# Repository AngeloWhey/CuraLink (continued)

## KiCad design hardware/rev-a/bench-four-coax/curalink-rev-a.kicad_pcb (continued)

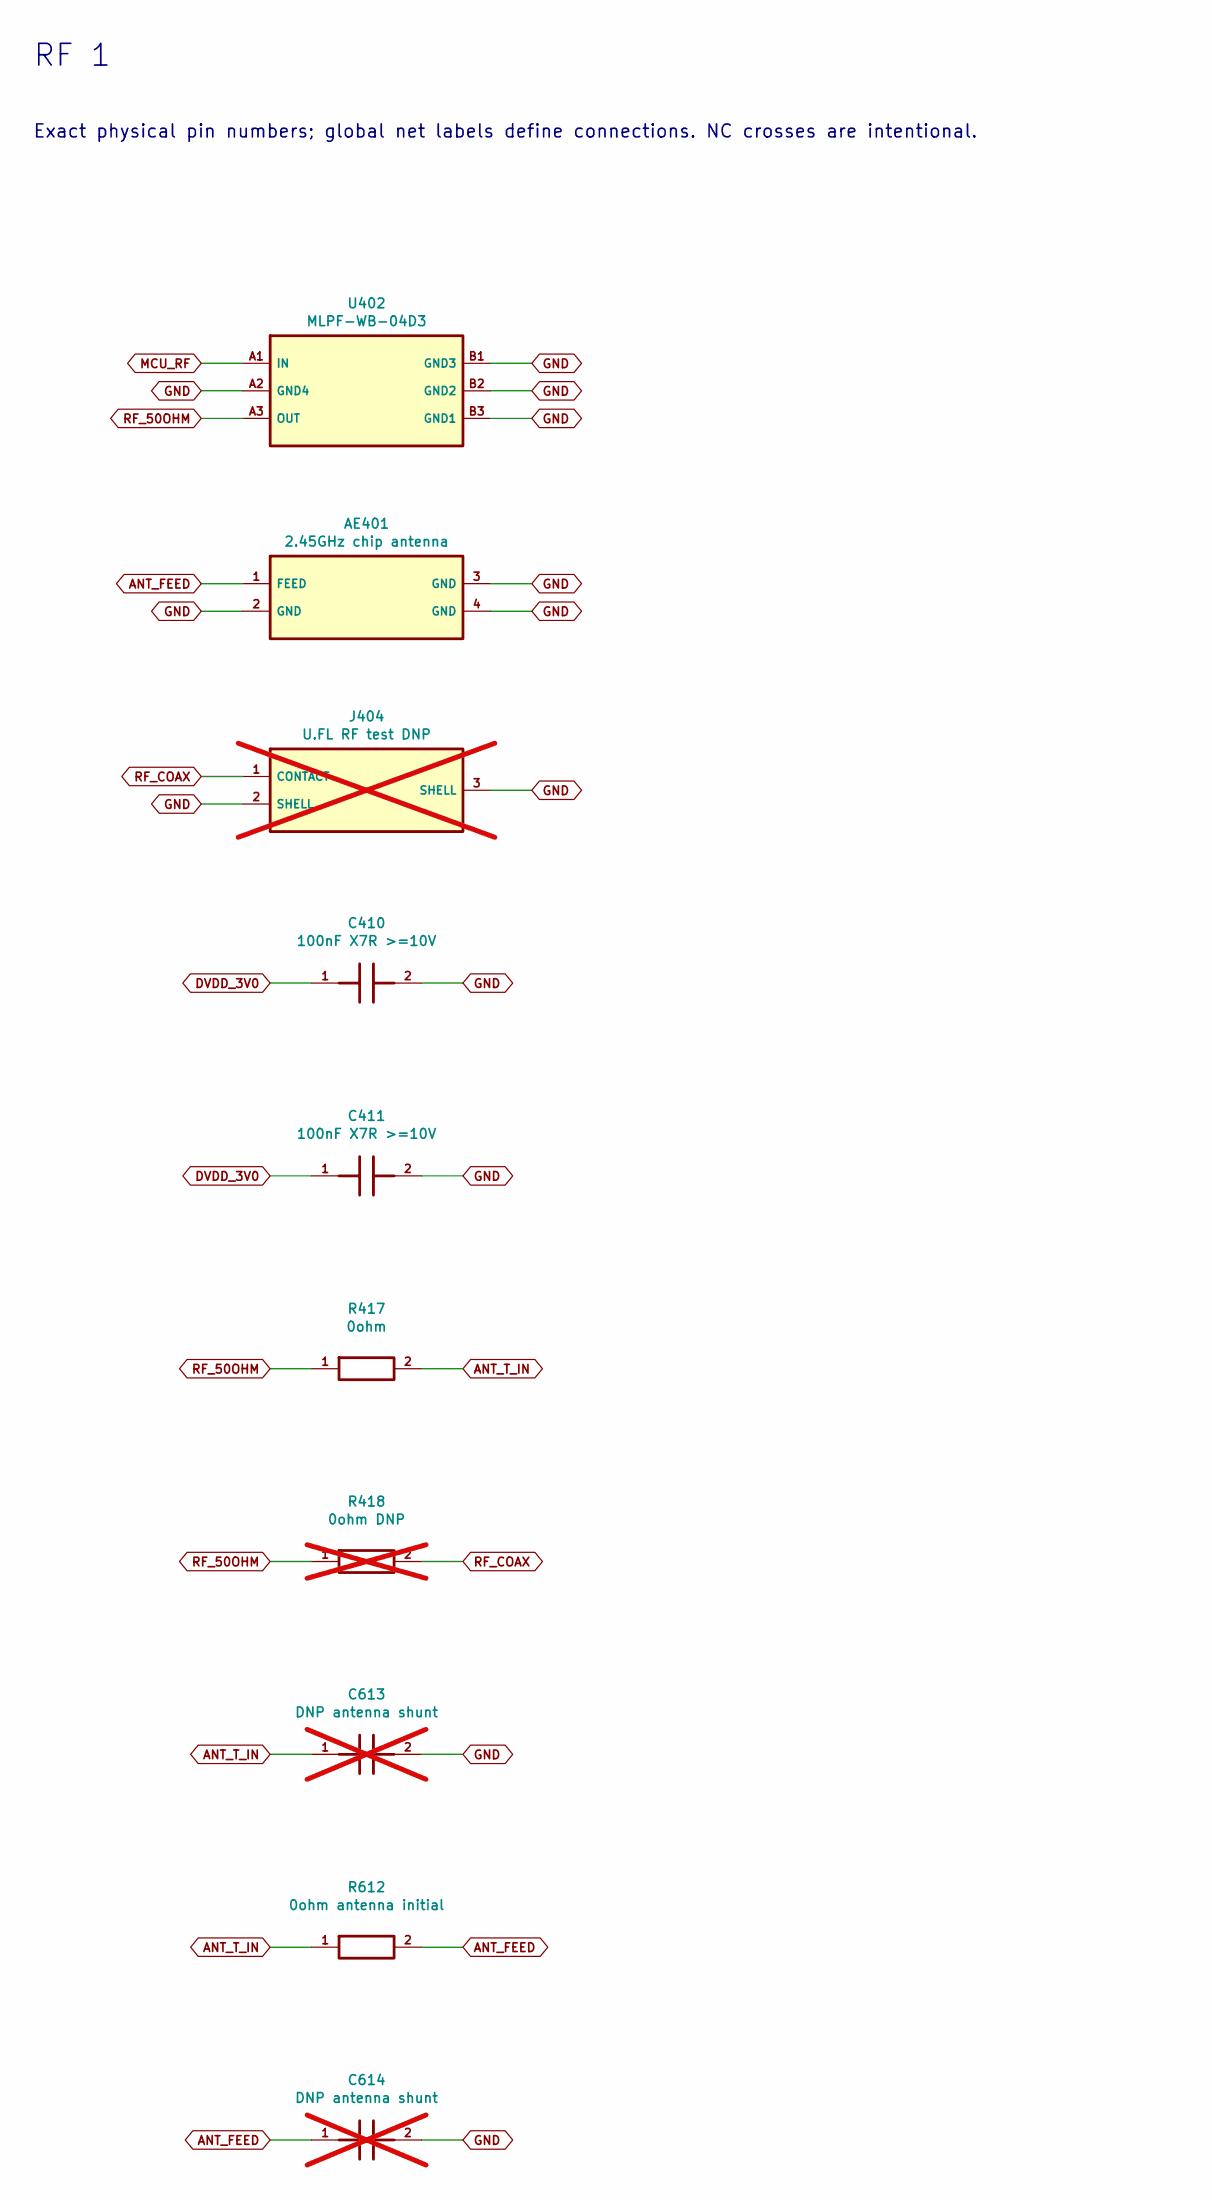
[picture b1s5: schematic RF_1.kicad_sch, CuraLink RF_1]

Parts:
AE401: 2.45GHz chip antenna; Johanson_2450AT18D0100001E; MPN 2450AT18D0100001E; LCSC C7450310
C410, C411: 100nF X7R >=10V; C_0402_1005Metric; MPN GRM155R71C104KA88D; LCSC C71629
C613, C614: DNP antenna shunt; C_0402_1005Metric; not fitted
J404: U.FL RF test DNP; UFL_Hirose_1SIG_2GND_3GND; MPN U.FL-R-SMT-1(80); LCSC C88374; not fitted
R417: 0ohm; R_0402_1005Metric; MPN 0402WGF0000TCE; LCSC C17168
R418: 0ohm DNP; R_0402_1005Metric; MPN 0402WGF0000TCE; LCSC C17168; not fitted
R612: 0ohm antenna initial; R_0402_1005Metric; MPN 0402WGF0000TCE; LCSC C17168
U402: MLPF-WB-04D3; MPN MLPF-WB-04D3; LCSC C22378853

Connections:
ANT_FEED: AE401.1 (FEED), C614.1, R612.2
ANT_T_IN: C613.1, R417.2, R612.1
DVDD_3V0: C410.1, C411.1; also elsewhere on the board
GND: AE401.2 (GND), AE401.3 (GND), AE401.4 (GND), C410.2, C411.2, C613.2, C614.2, J404.2 (SHELL), J404.3 (SHELL), U402.A2 (GND4), U402.B1 (GND3), U402.B2 (GND2), U402.B3 (GND1); also elsewhere on the board
MCU_RF: U402.A1 (IN); also elsewhere on the board
RF_50OHM: R417.1, R418.1, U402.A3 (OUT)
RF_COAX: J404.1 (CONTACT), R418.2

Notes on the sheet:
RF 1
Exact physical pin numbers; global net labels define connections. NC crosses are intentional.

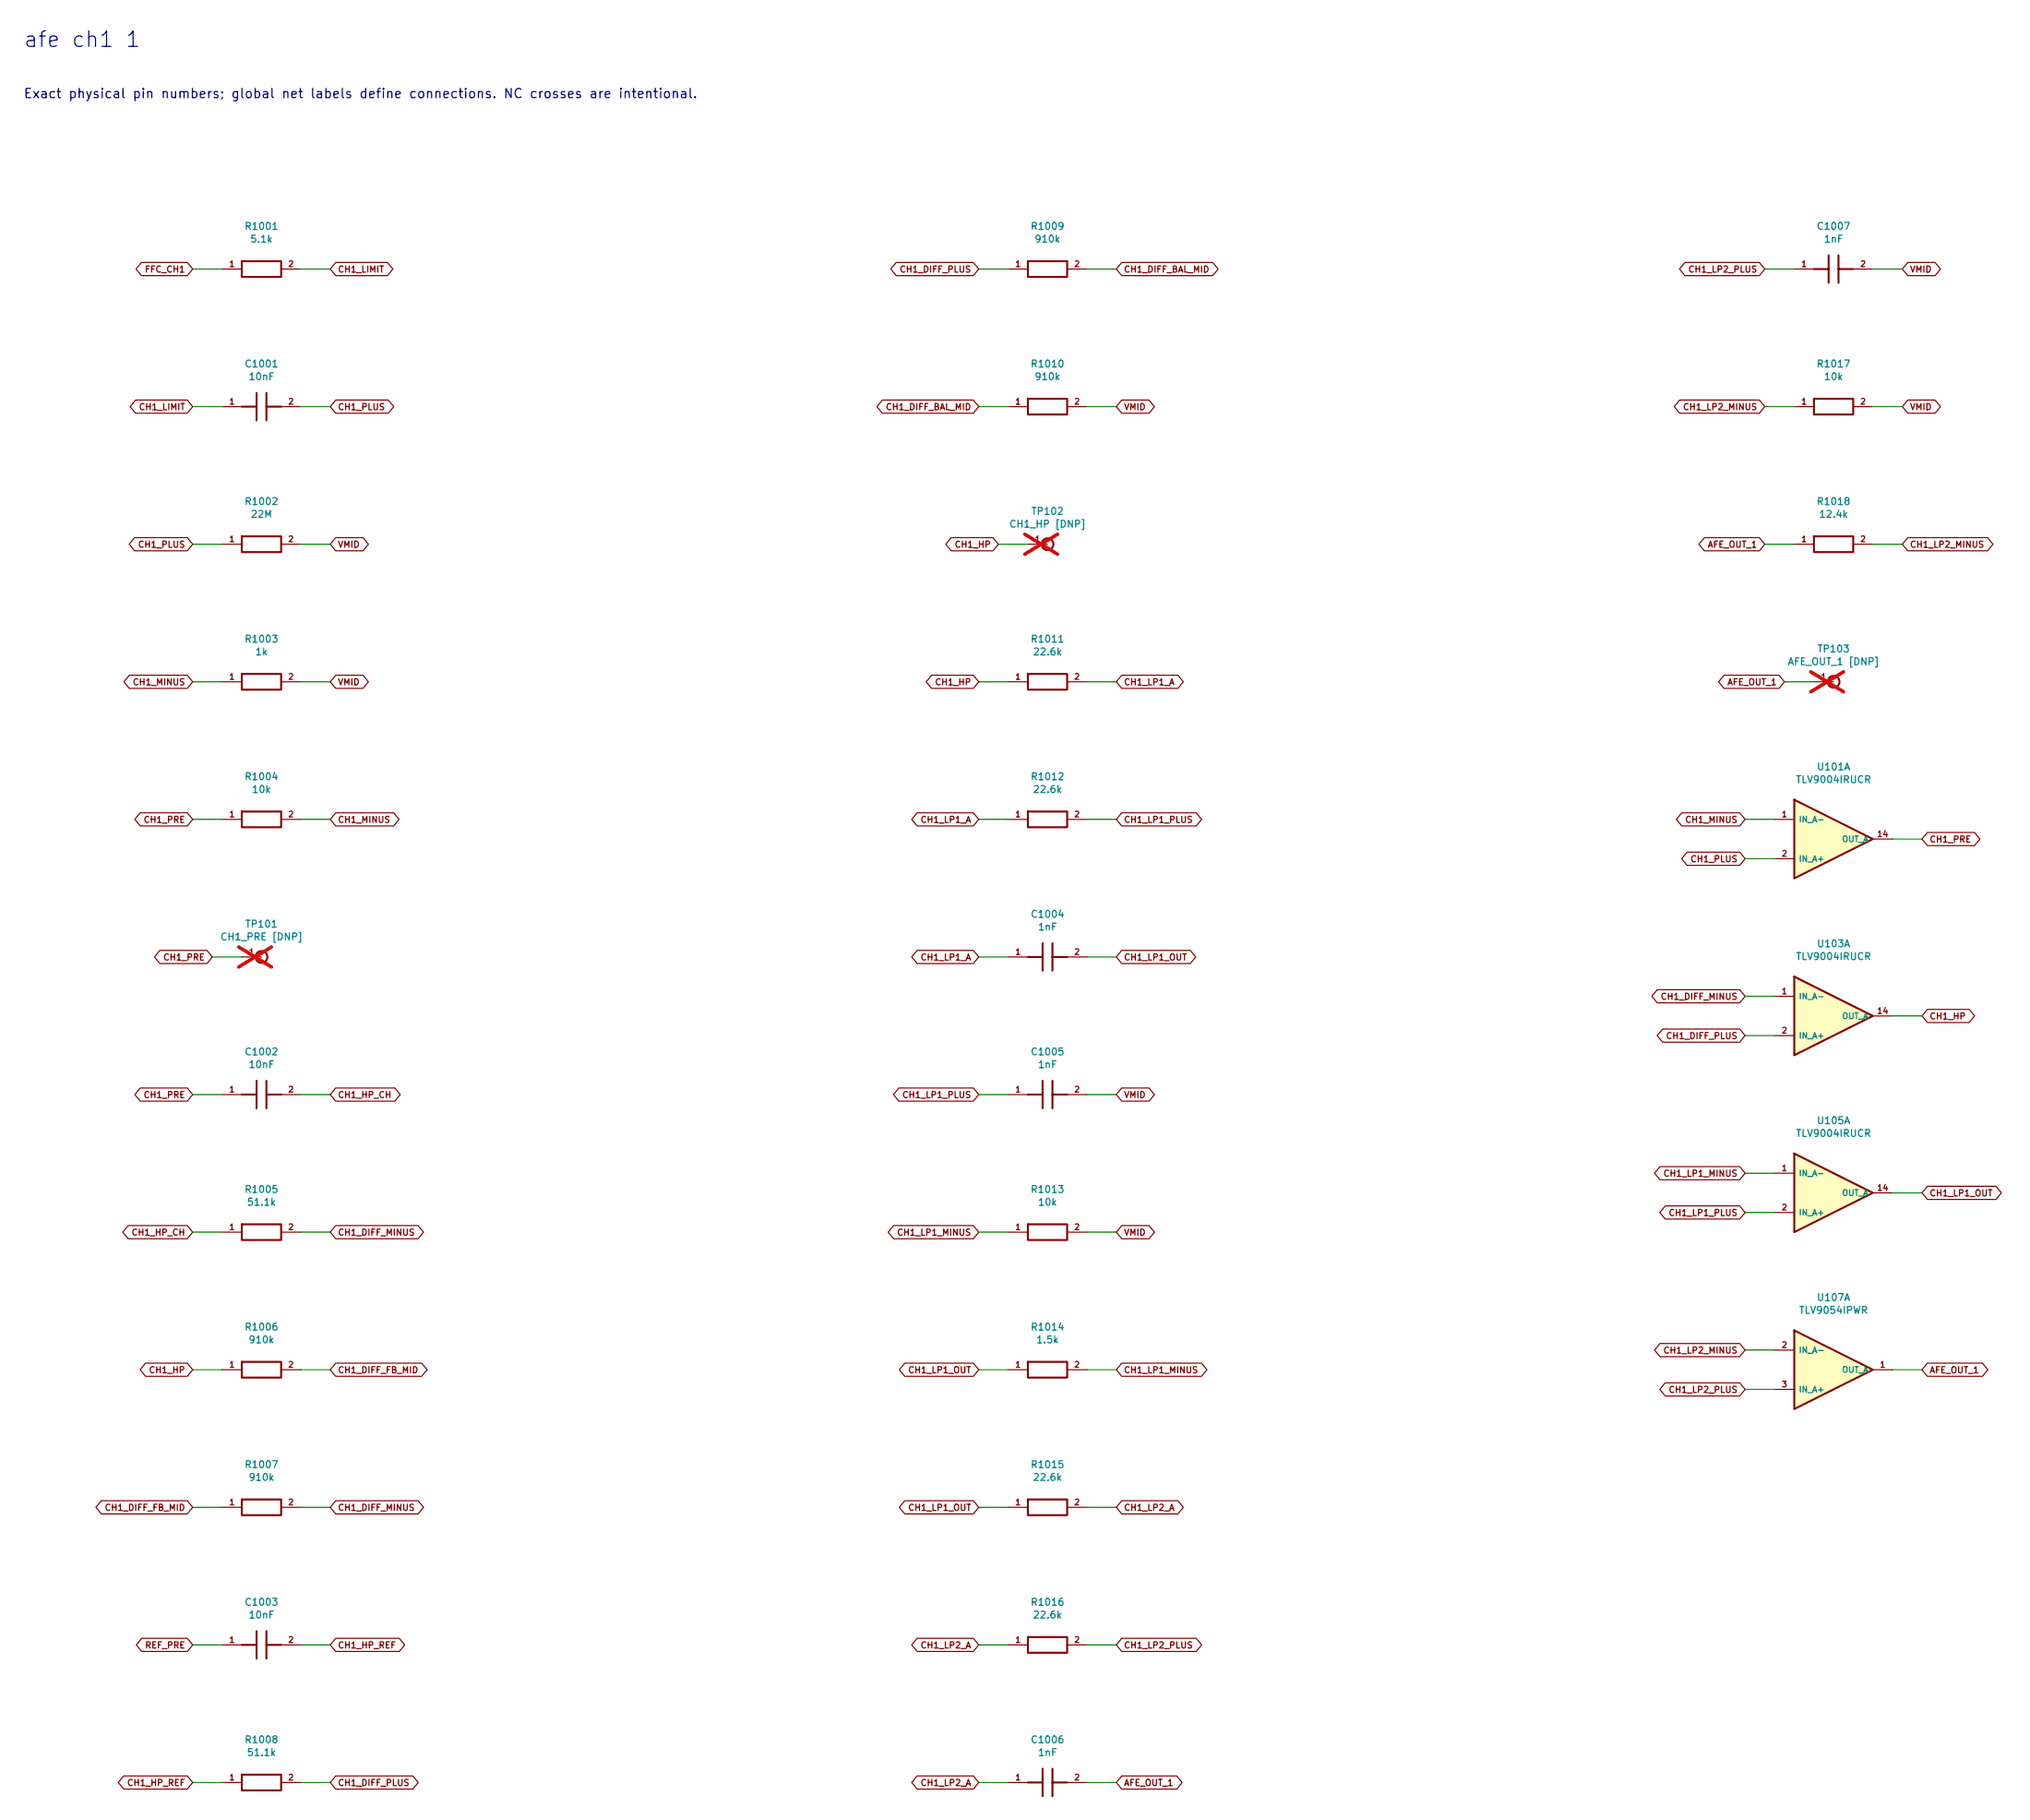
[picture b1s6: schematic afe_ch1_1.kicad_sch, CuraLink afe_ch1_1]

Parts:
C1001, C1002, C1003: 10nF; C_0603_1608Metric; MPN C0603C103F3GACTU; LCSC C2167903
C1004, C1005, C1006, C1007: 1nF; C_0603_1608Metric; MPN 0603CG102F500NT; LCSC C507408
R1001: 5.1k; R_0402_1005Metric; MPN 0402WGF5101TCE; LCSC C25905
R1002: 22M; R_0402_1005Metric; MPN 0402WGF2205TCE; LCSC C407703
R1003: 1k; R_0402_1005Metric; MPN RT0402BRD071KL; LCSC C852624
R1004, R1013, R1017: 10k; R_0402_1005Metric; MPN RT0402BRD0710KL; LCSC C190095
R1005, R1008: 51.1k; R_0402_1005Metric; MPN RT0402BRD0751K1L; LCSC C852827
R1006, R1007, R1009, R1010: 910k; R_0603_1608Metric; MPN ARG03BTC9103; LCSC C2686431
R1011, R1012, R1015, R1016: 22.6k; R_0402_1005Metric; MPN 0402WGF2262TCE; LCSC C26960
R1014: 1.5k; R_0402_1005Metric; MPN RT0402BRD071K5L; LCSC C281775
R1018: 12.4k; R_0402_1005Metric; MPN RT0402BRD0712K4L; LCSC C723611
TP101: CH1_PRE [DNP]; TestPoint_Pad_D1.0mm; not fitted
TP102: CH1_HP [DNP]; TestPoint_Pad_D1.0mm; not fitted
TP103: AFE_OUT_1 [DNP]; TestPoint_Pad_D1.0mm; not fitted
U101, U103, U105: TLV9004IRUCR; TLV_RUC14_X2QFN_2x2mm_NoEP; MPN TLV9004IRUCR; LCSC C2058192
U107: TLV9054IPWR; TSSOP-14_4.4x5mm_P0.65mm; MPN TLV9054IPWR; LCSC C2057744

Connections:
AFE_OUT_1: C1006.2, R1018.1, TP103.1, U107.1 (OUT_A); also elsewhere on the board
CH1_DIFF_BAL_MID: R1009.2, R1010.1
CH1_DIFF_FB_MID: R1006.2, R1007.1
CH1_DIFF_MINUS: R1005.2, R1007.2, U103.1 (IN_A-)
CH1_DIFF_PLUS: R1008.2, R1009.1, U103.2 (IN_A+)
CH1_HP: R1006.1, R1011.1, TP102.1, U103.14 (OUT_A)
CH1_HP_CH: C1002.2, R1005.1
CH1_HP_REF: C1003.2, R1008.1
CH1_LIMIT: C1001.1, R1001.2
CH1_LP1_A: C1004.1, R1011.2, R1012.1
CH1_LP1_MINUS: R1013.1, R1014.2, U105.1 (IN_A-)
CH1_LP1_OUT: C1004.2, R1014.1, R1015.1, U105.14 (OUT_A)
CH1_LP1_PLUS: C1005.1, R1012.2, U105.2 (IN_A+)
CH1_LP2_A: C1006.1, R1015.2, R1016.1
CH1_LP2_MINUS: R1017.1, R1018.2, U107.2 (IN_A-)
CH1_LP2_PLUS: C1007.1, R1016.2, U107.3 (IN_A+)
CH1_MINUS: R1003.1, R1004.2, U101.1 (IN_A-)
CH1_PLUS: C1001.2, R1002.1, U101.2 (IN_A+)
CH1_PRE: C1002.1, R1004.1, TP101.1, U101.14 (OUT_A)
FFC_CH1: R1001.1; also elsewhere on the board
REF_PRE: C1003.1; also elsewhere on the board
VMID: C1005.2, C1007.2, R1002.2, R1003.2, R1010.2, R1013.2, R1017.2; also elsewhere on the board

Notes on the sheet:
afe ch1 1
Exact physical pin numbers; global net labels define connections. NC crosses are intentional.

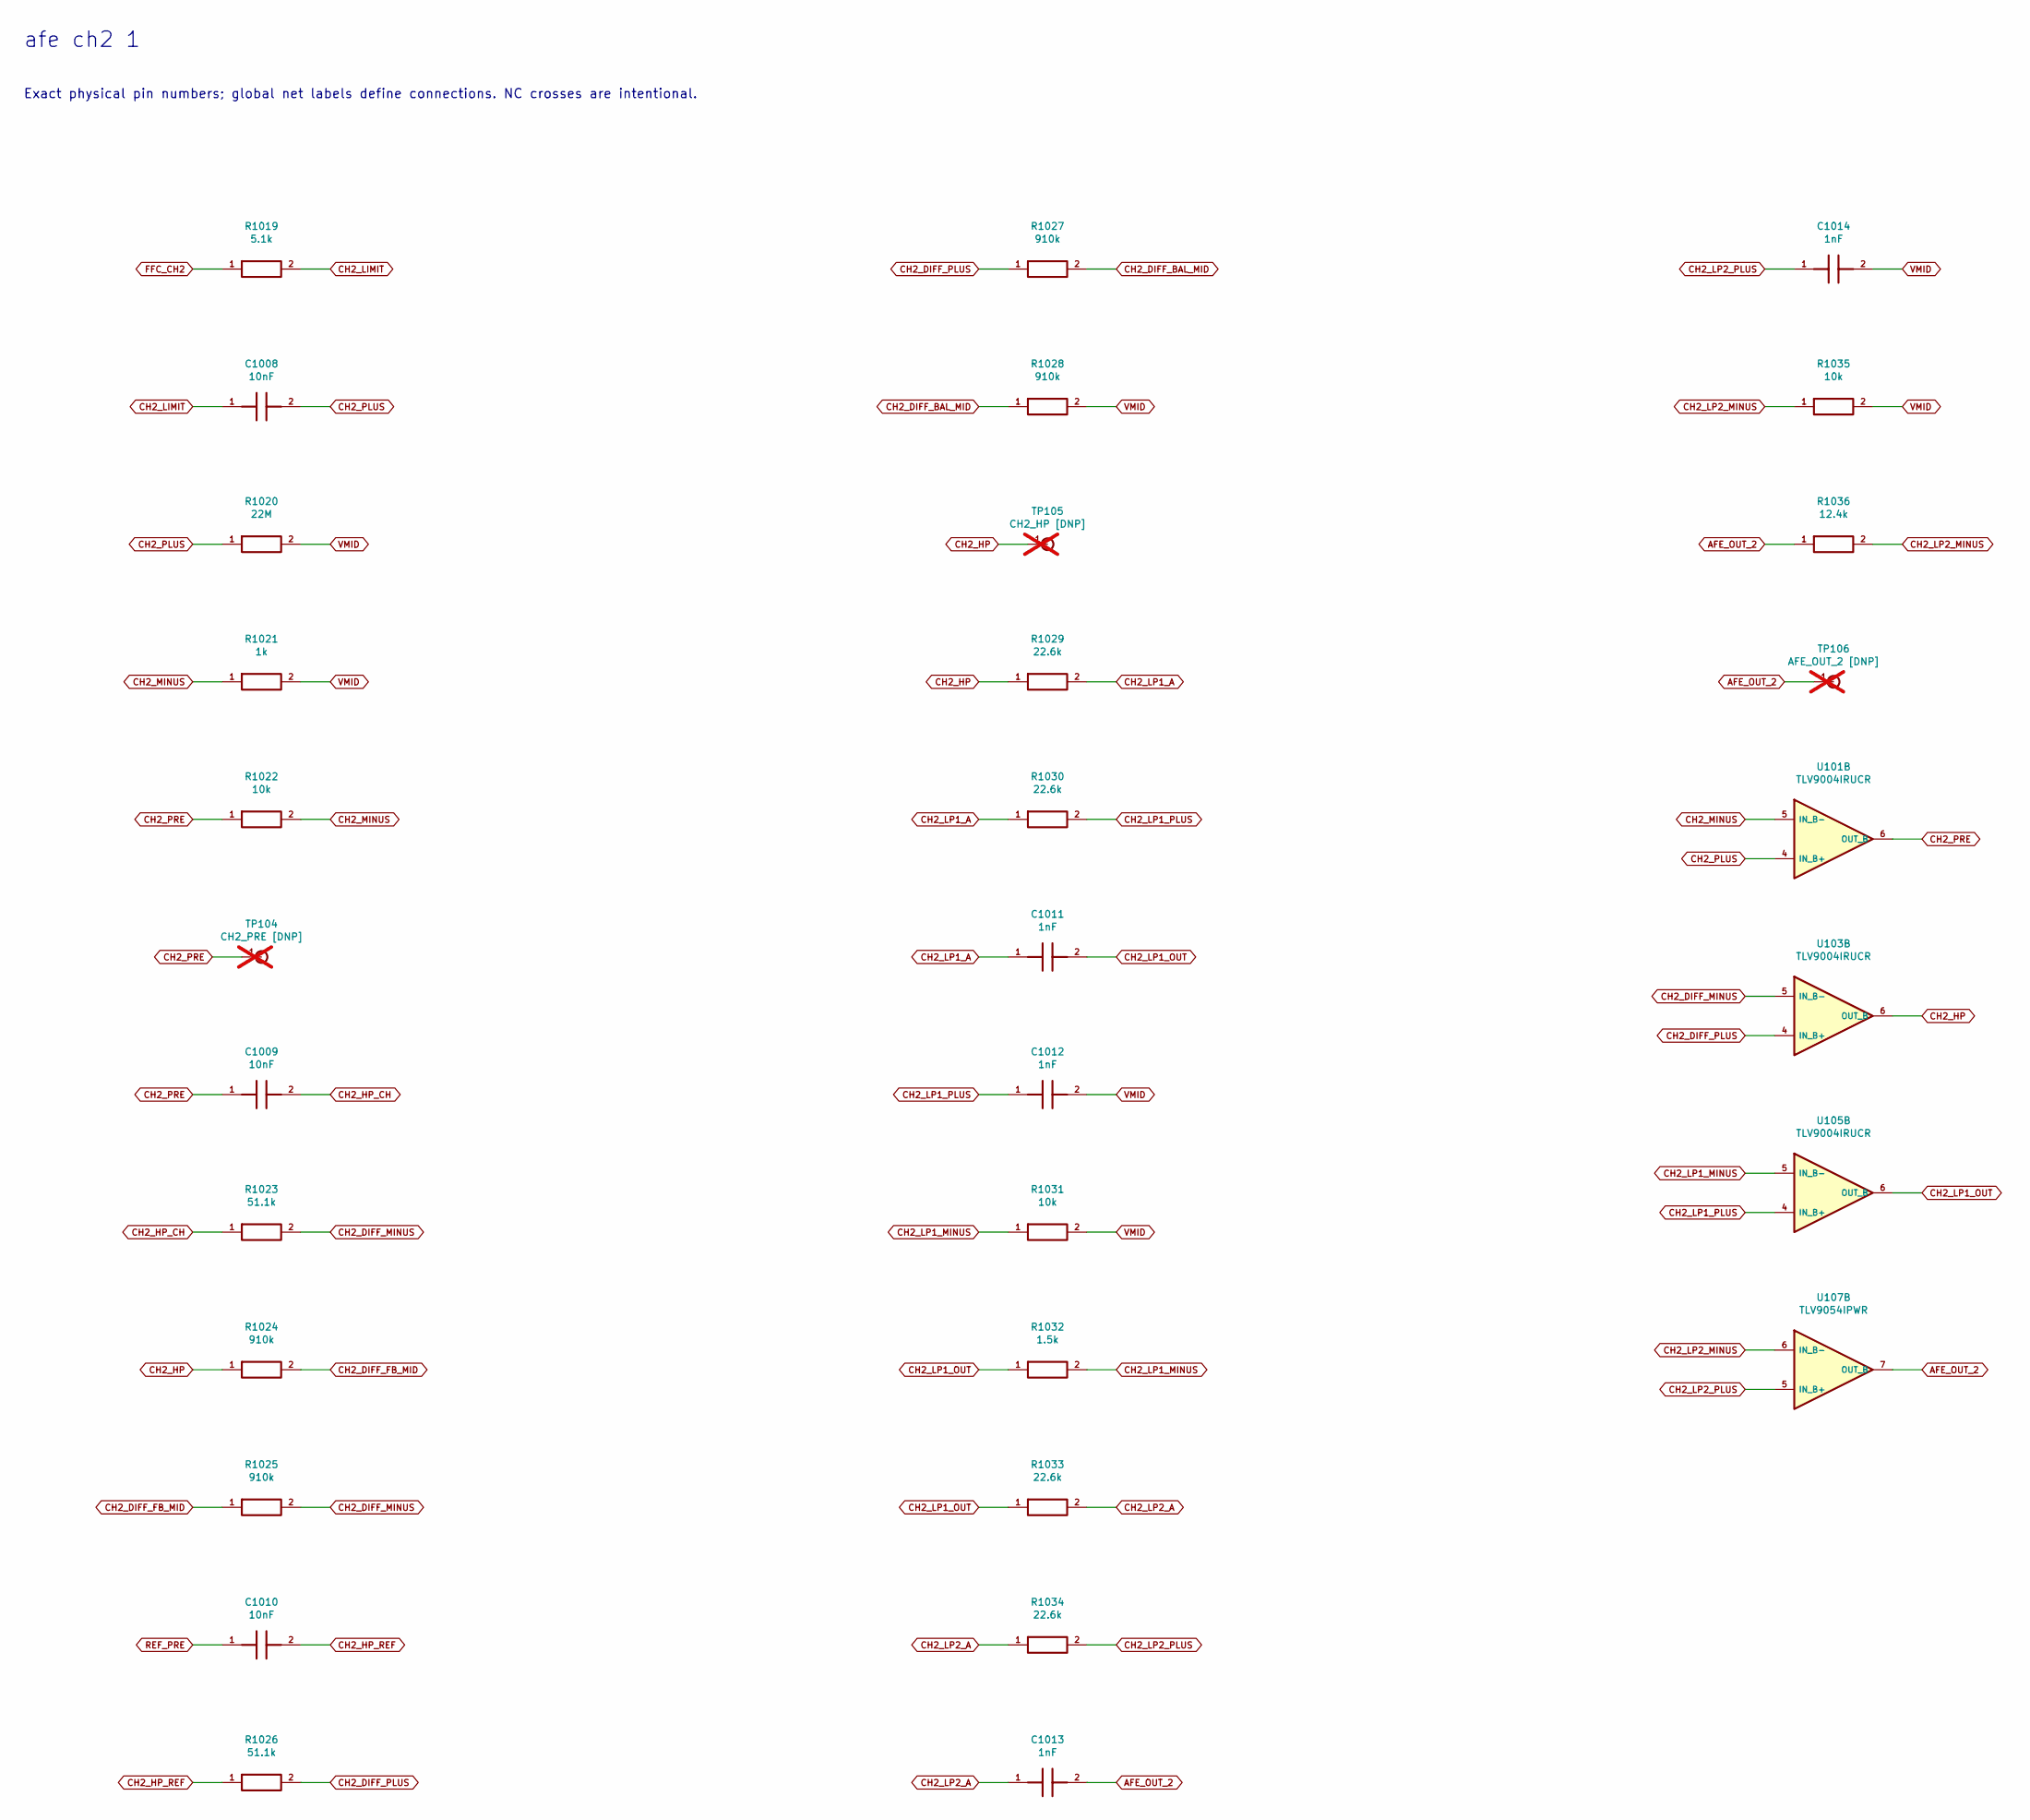
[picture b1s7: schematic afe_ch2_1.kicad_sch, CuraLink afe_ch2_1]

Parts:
C1008, C1009, C1010: 10nF; C_0603_1608Metric; MPN C0603C103F3GACTU; LCSC C2167903
C1011, C1012, C1013, C1014: 1nF; C_0603_1608Metric; MPN 0603CG102F500NT; LCSC C507408
R1019: 5.1k; R_0402_1005Metric; MPN 0402WGF5101TCE; LCSC C25905
R1020: 22M; R_0402_1005Metric; MPN 0402WGF2205TCE; LCSC C407703
R1021: 1k; R_0402_1005Metric; MPN RT0402BRD071KL; LCSC C852624
R1022, R1031, R1035: 10k; R_0402_1005Metric; MPN RT0402BRD0710KL; LCSC C190095
R1023, R1026: 51.1k; R_0402_1005Metric; MPN RT0402BRD0751K1L; LCSC C852827
R1024, R1025, R1027, R1028: 910k; R_0603_1608Metric; MPN ARG03BTC9103; LCSC C2686431
R1029, R1030, R1033, R1034: 22.6k; R_0402_1005Metric; MPN 0402WGF2262TCE; LCSC C26960
R1032: 1.5k; R_0402_1005Metric; MPN RT0402BRD071K5L; LCSC C281775
R1036: 12.4k; R_0402_1005Metric; MPN RT0402BRD0712K4L; LCSC C723611
TP104: CH2_PRE [DNP]; TestPoint_Pad_D1.0mm; not fitted
TP105: CH2_HP [DNP]; TestPoint_Pad_D1.0mm; not fitted
TP106: AFE_OUT_2 [DNP]; TestPoint_Pad_D1.0mm; not fitted
U101, U103, U105: TLV9004IRUCR; TLV_RUC14_X2QFN_2x2mm_NoEP; MPN TLV9004IRUCR; LCSC C2058192
U107: TLV9054IPWR; TSSOP-14_4.4x5mm_P0.65mm; MPN TLV9054IPWR; LCSC C2057744

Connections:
AFE_OUT_2: C1013.2, R1036.1, TP106.1, U107.7 (OUT_B); also elsewhere on the board
CH2_DIFF_BAL_MID: R1027.2, R1028.1
CH2_DIFF_FB_MID: R1024.2, R1025.1
CH2_DIFF_MINUS: R1023.2, R1025.2, U103.5 (IN_B-)
CH2_DIFF_PLUS: R1026.2, R1027.1, U103.4 (IN_B+)
CH2_HP: R1024.1, R1029.1, TP105.1, U103.6 (OUT_B)
CH2_HP_CH: C1009.2, R1023.1
CH2_HP_REF: C1010.2, R1026.1
CH2_LIMIT: C1008.1, R1019.2
CH2_LP1_A: C1011.1, R1029.2, R1030.1
CH2_LP1_MINUS: R1031.1, R1032.2, U105.5 (IN_B-)
CH2_LP1_OUT: C1011.2, R1032.1, R1033.1, U105.6 (OUT_B)
CH2_LP1_PLUS: C1012.1, R1030.2, U105.4 (IN_B+)
CH2_LP2_A: C1013.1, R1033.2, R1034.1
CH2_LP2_MINUS: R1035.1, R1036.2, U107.6 (IN_B-)
CH2_LP2_PLUS: C1014.1, R1034.2, U107.5 (IN_B+)
CH2_MINUS: R1021.1, R1022.2, U101.5 (IN_B-)
CH2_PLUS: C1008.2, R1020.1, U101.4 (IN_B+)
CH2_PRE: C1009.1, R1022.1, TP104.1, U101.6 (OUT_B)
FFC_CH2: R1019.1; also elsewhere on the board
REF_PRE: C1010.1; also elsewhere on the board
VMID: C1012.2, C1014.2, R1020.2, R1021.2, R1028.2, R1031.2, R1035.2; also elsewhere on the board

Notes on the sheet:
afe ch2 1
Exact physical pin numbers; global net labels define connections. NC crosses are intentional.

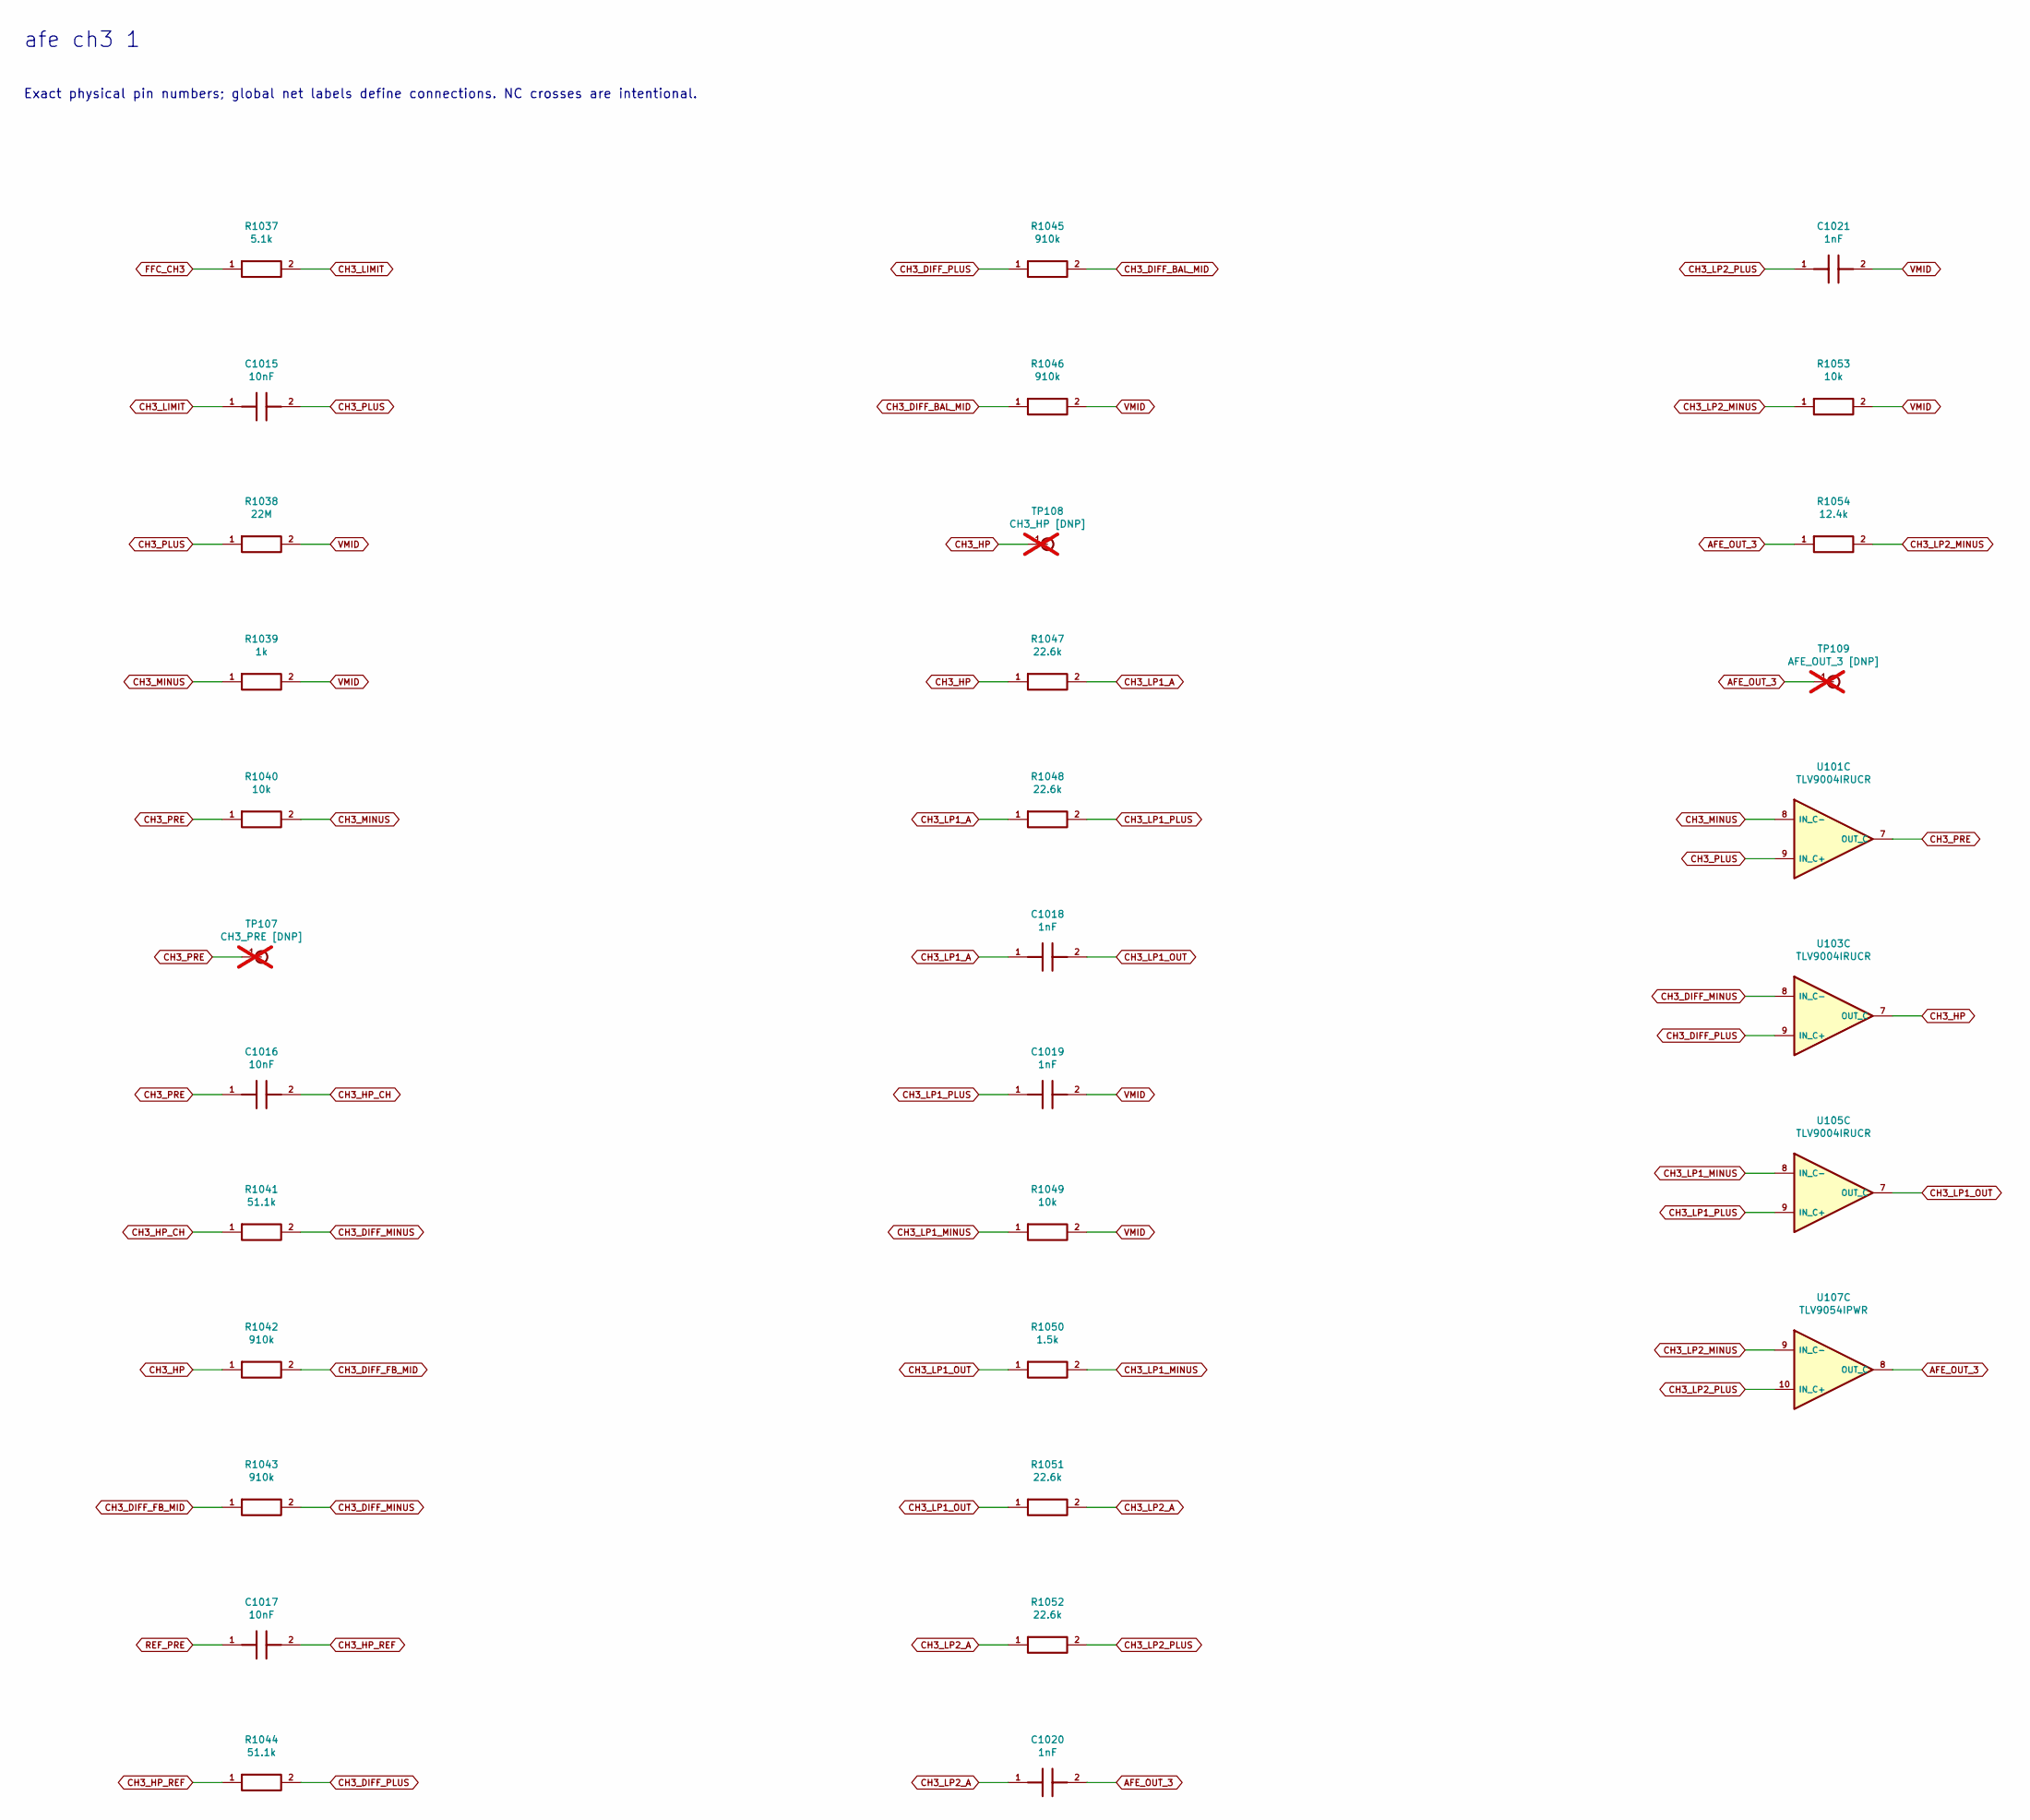
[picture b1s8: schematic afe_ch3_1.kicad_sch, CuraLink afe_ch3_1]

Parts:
C1015, C1016, C1017: 10nF; C_0603_1608Metric; MPN C0603C103F3GACTU; LCSC C2167903
C1018, C1019, C1020, C1021: 1nF; C_0603_1608Metric; MPN 0603CG102F500NT; LCSC C507408
R1037: 5.1k; R_0402_1005Metric; MPN 0402WGF5101TCE; LCSC C25905
R1038: 22M; R_0402_1005Metric; MPN 0402WGF2205TCE; LCSC C407703
R1039: 1k; R_0402_1005Metric; MPN RT0402BRD071KL; LCSC C852624
R1040, R1049, R1053: 10k; R_0402_1005Metric; MPN RT0402BRD0710KL; LCSC C190095
R1041, R1044: 51.1k; R_0402_1005Metric; MPN RT0402BRD0751K1L; LCSC C852827
R1042, R1043, R1045, R1046: 910k; R_0603_1608Metric; MPN ARG03BTC9103; LCSC C2686431
R1047, R1048, R1051, R1052: 22.6k; R_0402_1005Metric; MPN 0402WGF2262TCE; LCSC C26960
R1050: 1.5k; R_0402_1005Metric; MPN RT0402BRD071K5L; LCSC C281775
R1054: 12.4k; R_0402_1005Metric; MPN RT0402BRD0712K4L; LCSC C723611
TP107: CH3_PRE [DNP]; TestPoint_Pad_D1.0mm; not fitted
TP108: CH3_HP [DNP]; TestPoint_Pad_D1.0mm; not fitted
TP109: AFE_OUT_3 [DNP]; TestPoint_Pad_D1.0mm; not fitted
U101, U103, U105: TLV9004IRUCR; TLV_RUC14_X2QFN_2x2mm_NoEP; MPN TLV9004IRUCR; LCSC C2058192
U107: TLV9054IPWR; TSSOP-14_4.4x5mm_P0.65mm; MPN TLV9054IPWR; LCSC C2057744

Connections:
AFE_OUT_3: C1020.2, R1054.1, TP109.1, U107.8 (OUT_C); also elsewhere on the board
CH3_DIFF_BAL_MID: R1045.2, R1046.1
CH3_DIFF_FB_MID: R1042.2, R1043.1
CH3_DIFF_MINUS: R1041.2, R1043.2, U103.8 (IN_C-)
CH3_DIFF_PLUS: R1044.2, R1045.1, U103.9 (IN_C+)
CH3_HP: R1042.1, R1047.1, TP108.1, U103.7 (OUT_C)
CH3_HP_CH: C1016.2, R1041.1
CH3_HP_REF: C1017.2, R1044.1
CH3_LIMIT: C1015.1, R1037.2
CH3_LP1_A: C1018.1, R1047.2, R1048.1
CH3_LP1_MINUS: R1049.1, R1050.2, U105.8 (IN_C-)
CH3_LP1_OUT: C1018.2, R1050.1, R1051.1, U105.7 (OUT_C)
CH3_LP1_PLUS: C1019.1, R1048.2, U105.9 (IN_C+)
CH3_LP2_A: C1020.1, R1051.2, R1052.1
CH3_LP2_MINUS: R1053.1, R1054.2, U107.9 (IN_C-)
CH3_LP2_PLUS: C1021.1, R1052.2, U107.10 (IN_C+)
CH3_MINUS: R1039.1, R1040.2, U101.8 (IN_C-)
CH3_PLUS: C1015.2, R1038.1, U101.9 (IN_C+)
CH3_PRE: C1016.1, R1040.1, TP107.1, U101.7 (OUT_C)
FFC_CH3: R1037.1; also elsewhere on the board
REF_PRE: C1017.1; also elsewhere on the board
VMID: C1019.2, C1021.2, R1038.2, R1039.2, R1046.2, R1049.2, R1053.2; also elsewhere on the board

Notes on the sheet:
afe ch3 1
Exact physical pin numbers; global net labels define connections. NC crosses are intentional.

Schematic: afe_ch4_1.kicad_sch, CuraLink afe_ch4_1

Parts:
C1022, C1023, C1024: 10nF; C_0603_1608Metric; MPN C0603C103F3GACTU; LCSC C2167903
C1025, C1026, C1027, C1028: 1nF; C_0603_1608Metric; MPN 0603CG102F500NT; LCSC C507408
R1055: 5.1k; R_0402_1005Metric; MPN 0402WGF5101TCE; LCSC C25905
R1056: 22M; R_0402_1005Metric; MPN 0402WGF2205TCE; LCSC C407703
R1057: 1k; R_0402_1005Metric; MPN RT0402BRD071KL; LCSC C852624
R1058, R1067, R1071: 10k; R_0402_1005Metric; MPN RT0402BRD0710KL; LCSC C190095
R1059, R1062: 51.1k; R_0402_1005Metric; MPN RT0402BRD0751K1L; LCSC C852827
R1060, R1061, R1063, R1064: 910k; R_0603_1608Metric; MPN ARG03BTC9103; LCSC C2686431
R1065, R1066, R1069, R1070: 22.6k; R_0402_1005Metric; MPN 0402WGF2262TCE; LCSC C26960
R1068: 1.5k; R_0402_1005Metric; MPN RT0402BRD071K5L; LCSC C281775
R1072: 12.4k; R_0402_1005Metric; MPN RT0402BRD0712K4L; LCSC C723611
TP110: CH4_PRE [DNP]; TestPoint_Pad_D1.0mm; not fitted
TP111: CH4_HP [DNP]; TestPoint_Pad_D1.0mm; not fitted
TP112: AFE_OUT_4 [DNP]; TestPoint_Pad_D1.0mm; not fitted
U101, U103, U105: TLV9004IRUCR; TLV_RUC14_X2QFN_2x2mm_NoEP; MPN TLV9004IRUCR; LCSC C2058192
U107: TLV9054IPWR; TSSOP-14_4.4x5mm_P0.65mm; MPN TLV9054IPWR; LCSC C2057744

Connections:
AFE_OUT_4: C1027.2, R1072.1, TP112.1, U107.14 (OUT_D); also elsewhere on the board
CH4_DIFF_BAL_MID: R1063.2, R1064.1
CH4_DIFF_FB_MID: R1060.2, R1061.1
CH4_DIFF_MINUS: R1059.2, R1061.2, U103.12 (IN_D-)
CH4_DIFF_PLUS: R1062.2, R1063.1, U103.11 (IN_D+)
CH4_HP: R1060.1, R1065.1, TP111.1, U103.13 (OUT_D)
CH4_HP_CH: C1023.2, R1059.1
CH4_HP_REF: C1024.2, R1062.1
CH4_LIMIT: C1022.1, R1055.2
CH4_LP1_A: C1025.1, R1065.2, R1066.1
CH4_LP1_MINUS: R1067.1, R1068.2, U105.12 (IN_D-)
CH4_LP1_OUT: C1025.2, R1068.1, R1069.1, U105.13 (OUT_D)
CH4_LP1_PLUS: C1026.1, R1066.2, U105.11 (IN_D+)
CH4_LP2_A: C1027.1, R1069.2, R1070.1
CH4_LP2_MINUS: R1071.1, R1072.2, U107.13 (IN_D-)
CH4_LP2_PLUS: C1028.1, R1070.2, U107.12 (IN_D+)
CH4_MINUS: R1057.1, R1058.2, U101.12 (IN_D-)
CH4_PLUS: C1022.2, R1056.1, U101.11 (IN_D+)
CH4_PRE: C1023.1, R1058.1, TP110.1, U101.13 (OUT_D)
FFC_CH4: R1055.1; also elsewhere on the board
REF_PRE: C1024.1; also elsewhere on the board
VMID: C1026.2, C1028.2, R1056.2, R1057.2, R1064.2, R1067.2, R1071.2; also elsewhere on the board

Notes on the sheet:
afe ch4 1
Exact physical pin numbers; global net labels define connections. NC crosses are intentional.
